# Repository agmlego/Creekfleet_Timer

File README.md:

Creekfleet Timer
================

Automated start sequencer for the [Creekfleet](https://creekfleet.org) sailing group.

By default, runs the following sequence for each of the number of requested starts:

| Horns             | Time to start |
| ----------------- | ------------- |
| 3 long            | 3:00          |
| 2 long            | 2:00          |
| 1 long, 3 short   | 1:30          |
| 1 long            | 1:00          |
| 3 short           | 0:30          |
| 2 short           | 0:20          |
| 1 short           | 0:10          |
| 1 short           | 0:05          |
| 1 short           | 0:04          |
| 1 short           | 0:03          |
| 1 short           | 0:02          |
| 1 short           | 0:01          |
| 1 long            | START         |

Also has a mode selectable during idle operation for the ISAF Rule 26 start:

| Horns             | Time to start |
| ----------------- | ------------- |
| 1 short           | 5:00          |
| 1 short           | 4:00          |
| 1 long            | 1:00          |
| 1 short           | START         |

## Pins

| Function      | Arduino Pin          |
| ------------- | -------------------- |
| Horn          | D12                  |
| Compressor    | D11                  |
| Pressure Gauge| D35 (A16)            |
| UP.LED        | D24                  |
| UP.Switch     | D25 (active low)     |
| DOWN.LED      | D26                  |
| DOWN.Switch   | D27 (active low)     |
| SELECT.LED    | D28                  |
| SELECT.Switch | D29 (active low)     |
| BACK.LED      | D30                  |
| BACK.Switch   | D31 (active low)     |
| LCD.VO        | A22 (DAC1)           |
| LCD.RS        | D13                  |
| LCD.RW        | D14                  |
| LCD.E         | D15                  |
| LCD.DB0       | D16                  |
| LCD.DB1       | D17                  |
| LCD.DB2       | D18                  |
| LCD.DB3       | D19                  |
| LCD.DB4       | D20                  |
| LCD.DB5       | D21                  |
| LCD.DB6       | D22                  |
| LCD.DB7       | D23                  |
| LCD.Red BL    | D36 (PWM)            |
| LCD.Green BL  | D38 (PWM)            |
| LCD.Blue BL   | D37 (PWM)            |

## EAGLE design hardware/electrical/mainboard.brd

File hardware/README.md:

Creekfleet Timer Hardware
=========================

EAGLE design files, case CAD files.

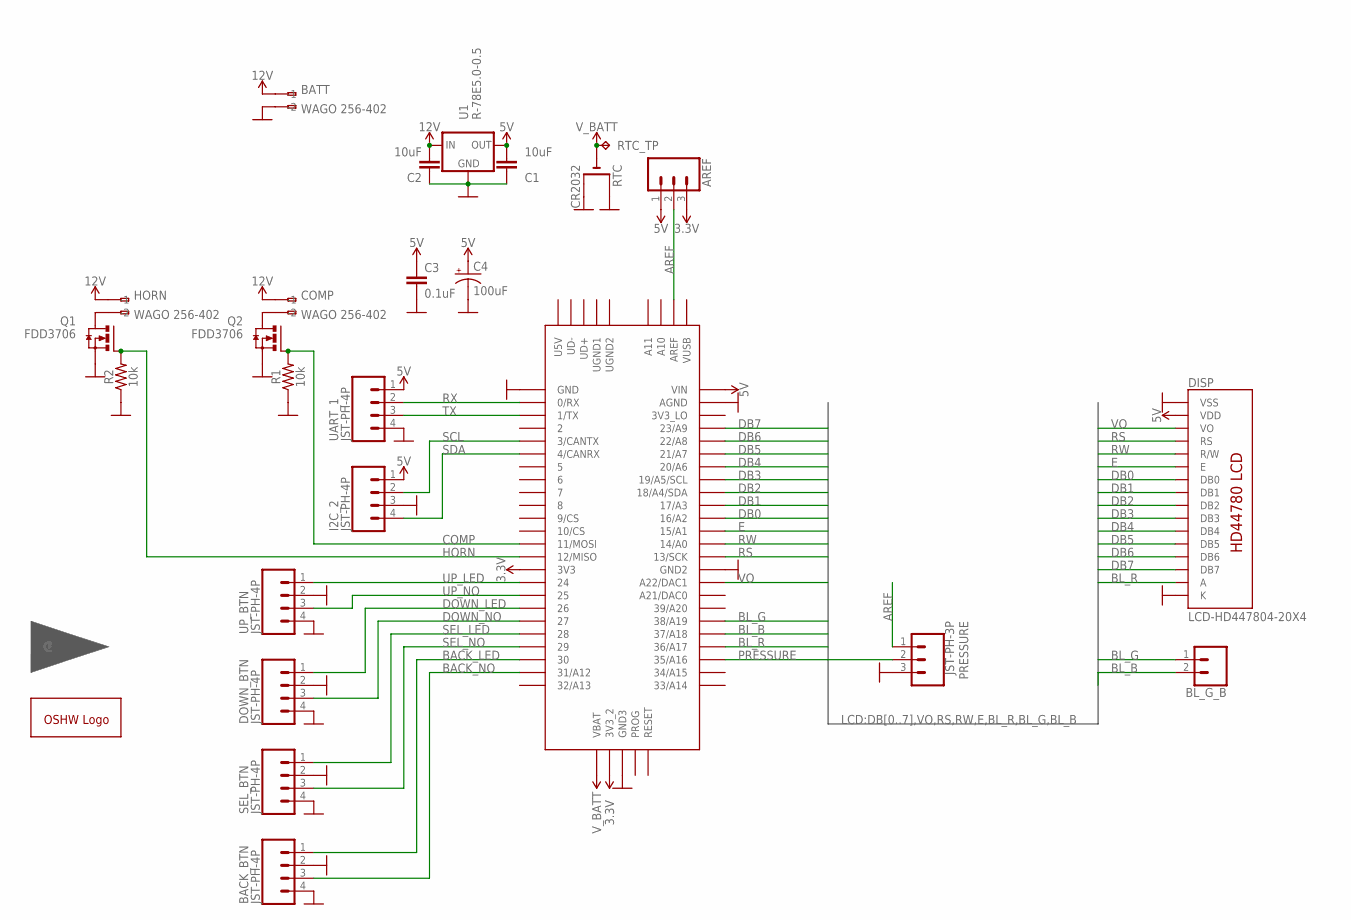
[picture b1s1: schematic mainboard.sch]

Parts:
AREF: CONN_03LOCK; 1X03_LOCK
BACK_BTN: JST-PH-4P; JST-4-PTH-VERT
BATT: WAGO 256-402; 255-402-5
BL_G_B: CONN_02; 1X02
C1, C2: 10uF; 0603
C3: 0.1uF; 0603
C4: 100uF; NIC_10X10.5_CAP
COMP: WAGO 256-402; 255-402-5
DISP: LCD-HD447804-20X4; LCD-20X4-4HOLES
DOWN_BTN: JST-PH-4P; JST-4-PTH-VERT
GOLD_ORB_SM1: OSHWLOGOLOGO8MM; OSHW_8MM
HORN: WAGO 256-402; 255-402-5
I2C_2: JST-PH-4P; JST-4-PTH-VERT
PRESSURE: JST-PH-3P; JST-3-PTH-VERT
Q1, Q2: FDD3706; D2PACK
R1, R2: 10k; 0603
RTC: CR2032; CR2032-SMD
RTC_TP: TPPAD1-17; P1-17
SEL_BTN: JST-PH-4P; JST-4-PTH-VERT
TEENSY: TEENSY_3.5/3.6
U1: R-78E5.0-0.5; DC-DC_CONVERTER_78XX
U$1: CFLOGO
UART_1: JST-PH-4P; JST-4-PTH-VERT
UP_BTN: JST-PH-4P; JST-4-PTH-VERT

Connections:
3.3V: AREF.3, TEENSY.3V3, TEENSY.3V3_2
5V: AREF.1, C1.2, C3.1, C4.+, DISP.P$2 (VDD), I2C_2.1, TEENSY.VIN, U1.VOUT (OUT), UART_1.1
12V: BATT.A1 (-1), C2.2, COMP.A1 (-1), HORN.A1 (-1), U1.VIN (IN)
AREF: AREF.2, PRESSURE.1, TEENSY.AREF
BACK_LED: BACK_BTN.1, TEENSY.30
BACK_NO: BACK_BTN.3, TEENSY.31/A12
BL_B: BL_G_B.2, TEENSY.37/A18
BL_G: BL_G_B.1, TEENSY.38/A19
BL_R: DISP.P$15 (A), TEENSY.36/A17
COMP: Q2.1 (G), R1.2, TEENSY.11/MOSI
DB0: DISP.P$7 (DB0), TEENSY.16/A2
DB1: DISP.P$8 (DB1), TEENSY.17/A3
DB2: DISP.P$9 (DB2), TEENSY.18/A4/SDA
DB3: DISP.P$10 (DB3), TEENSY.19/A5/SCL
DB4: DISP.P$11 (DB4), TEENSY.20/A6
DB5: DISP.P$12 (DB5), TEENSY.21/A7
DB6: DISP.P$13 (DB6), TEENSY.22/A8
DB7: DISP.P$14 (DB7), TEENSY.23/A9
DOWN_LED: DOWN_BTN.1, TEENSY.26
DOWN_NO: DOWN_BTN.3, TEENSY.27
E: DISP.P$6 (E), TEENSY.15/A1
GND: BACK_BTN.2, BACK_BTN.4, BATT.A2 (-2), C1.1, C2.1, C3.2, C4.-, DISP.P$1 (VSS), DISP.P$16 (K), DOWN_BTN.2, DOWN_BTN.4, I2C_2.3, PRESSURE.3, Q1.3 (S), Q2.3 (S), R1.1, R2.1, RTC.+$1 (+), RTC.+$2 (+1), SEL_BTN.2, SEL_BTN.4, TEENSY.AGND, TEENSY.GND, TEENSY.GND2, TEENSY.GND3, U1.GND, UART_1.4, UP_BTN.2, UP_BTN.4
HORN: Q1.1 (G), R2.2, TEENSY.12/MISO
unnamed: HORN.A2 (-2), Q1.2 (D)
unnamed: COMP.A2 (-2), Q2.2 (D)
PRESSURE: PRESSURE.2, TEENSY.35/A16
RS: DISP.P$4 (RS), TEENSY.13/SCK
RW: DISP.P$5 (R/W), TEENSY.14/A0
RX: TEENSY.0/RX, UART_1.2
SCL: I2C_2.2, TEENSY.3/CANTX
SDA: I2C_2.4, TEENSY.4/CANRX
SEL_LED: SEL_BTN.1, TEENSY.28
SEL_NO: SEL_BTN.3, TEENSY.29
TX: TEENSY.1/TX, UART_1.3
UP_LED: TEENSY.24, UP_BTN.1
UP_NO: TEENSY.25, UP_BTN.3
VO: DISP.P$3 (VO), TEENSY.A22/DAC1
V_BATT: RTC.-, RTC_TP.TP, TEENSY.VBAT

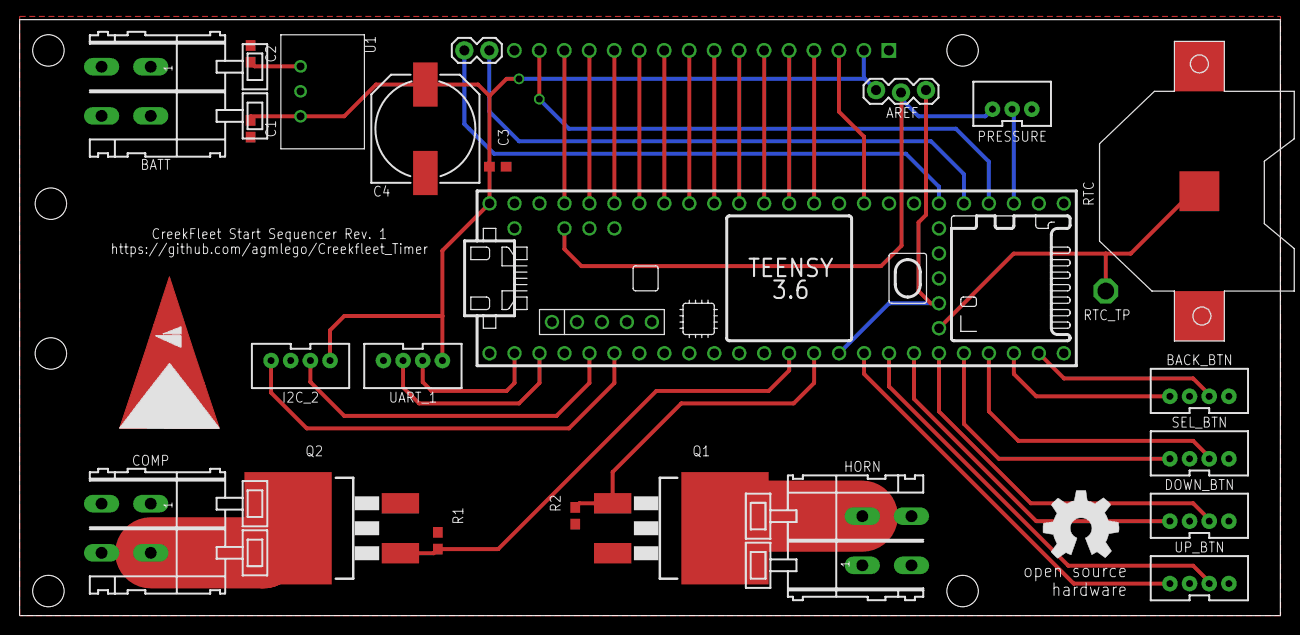
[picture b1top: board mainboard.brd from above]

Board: 2 copper layers, 128.2 x 60.6 mm, 27 parts (1 on the bottom side), 38 nets.

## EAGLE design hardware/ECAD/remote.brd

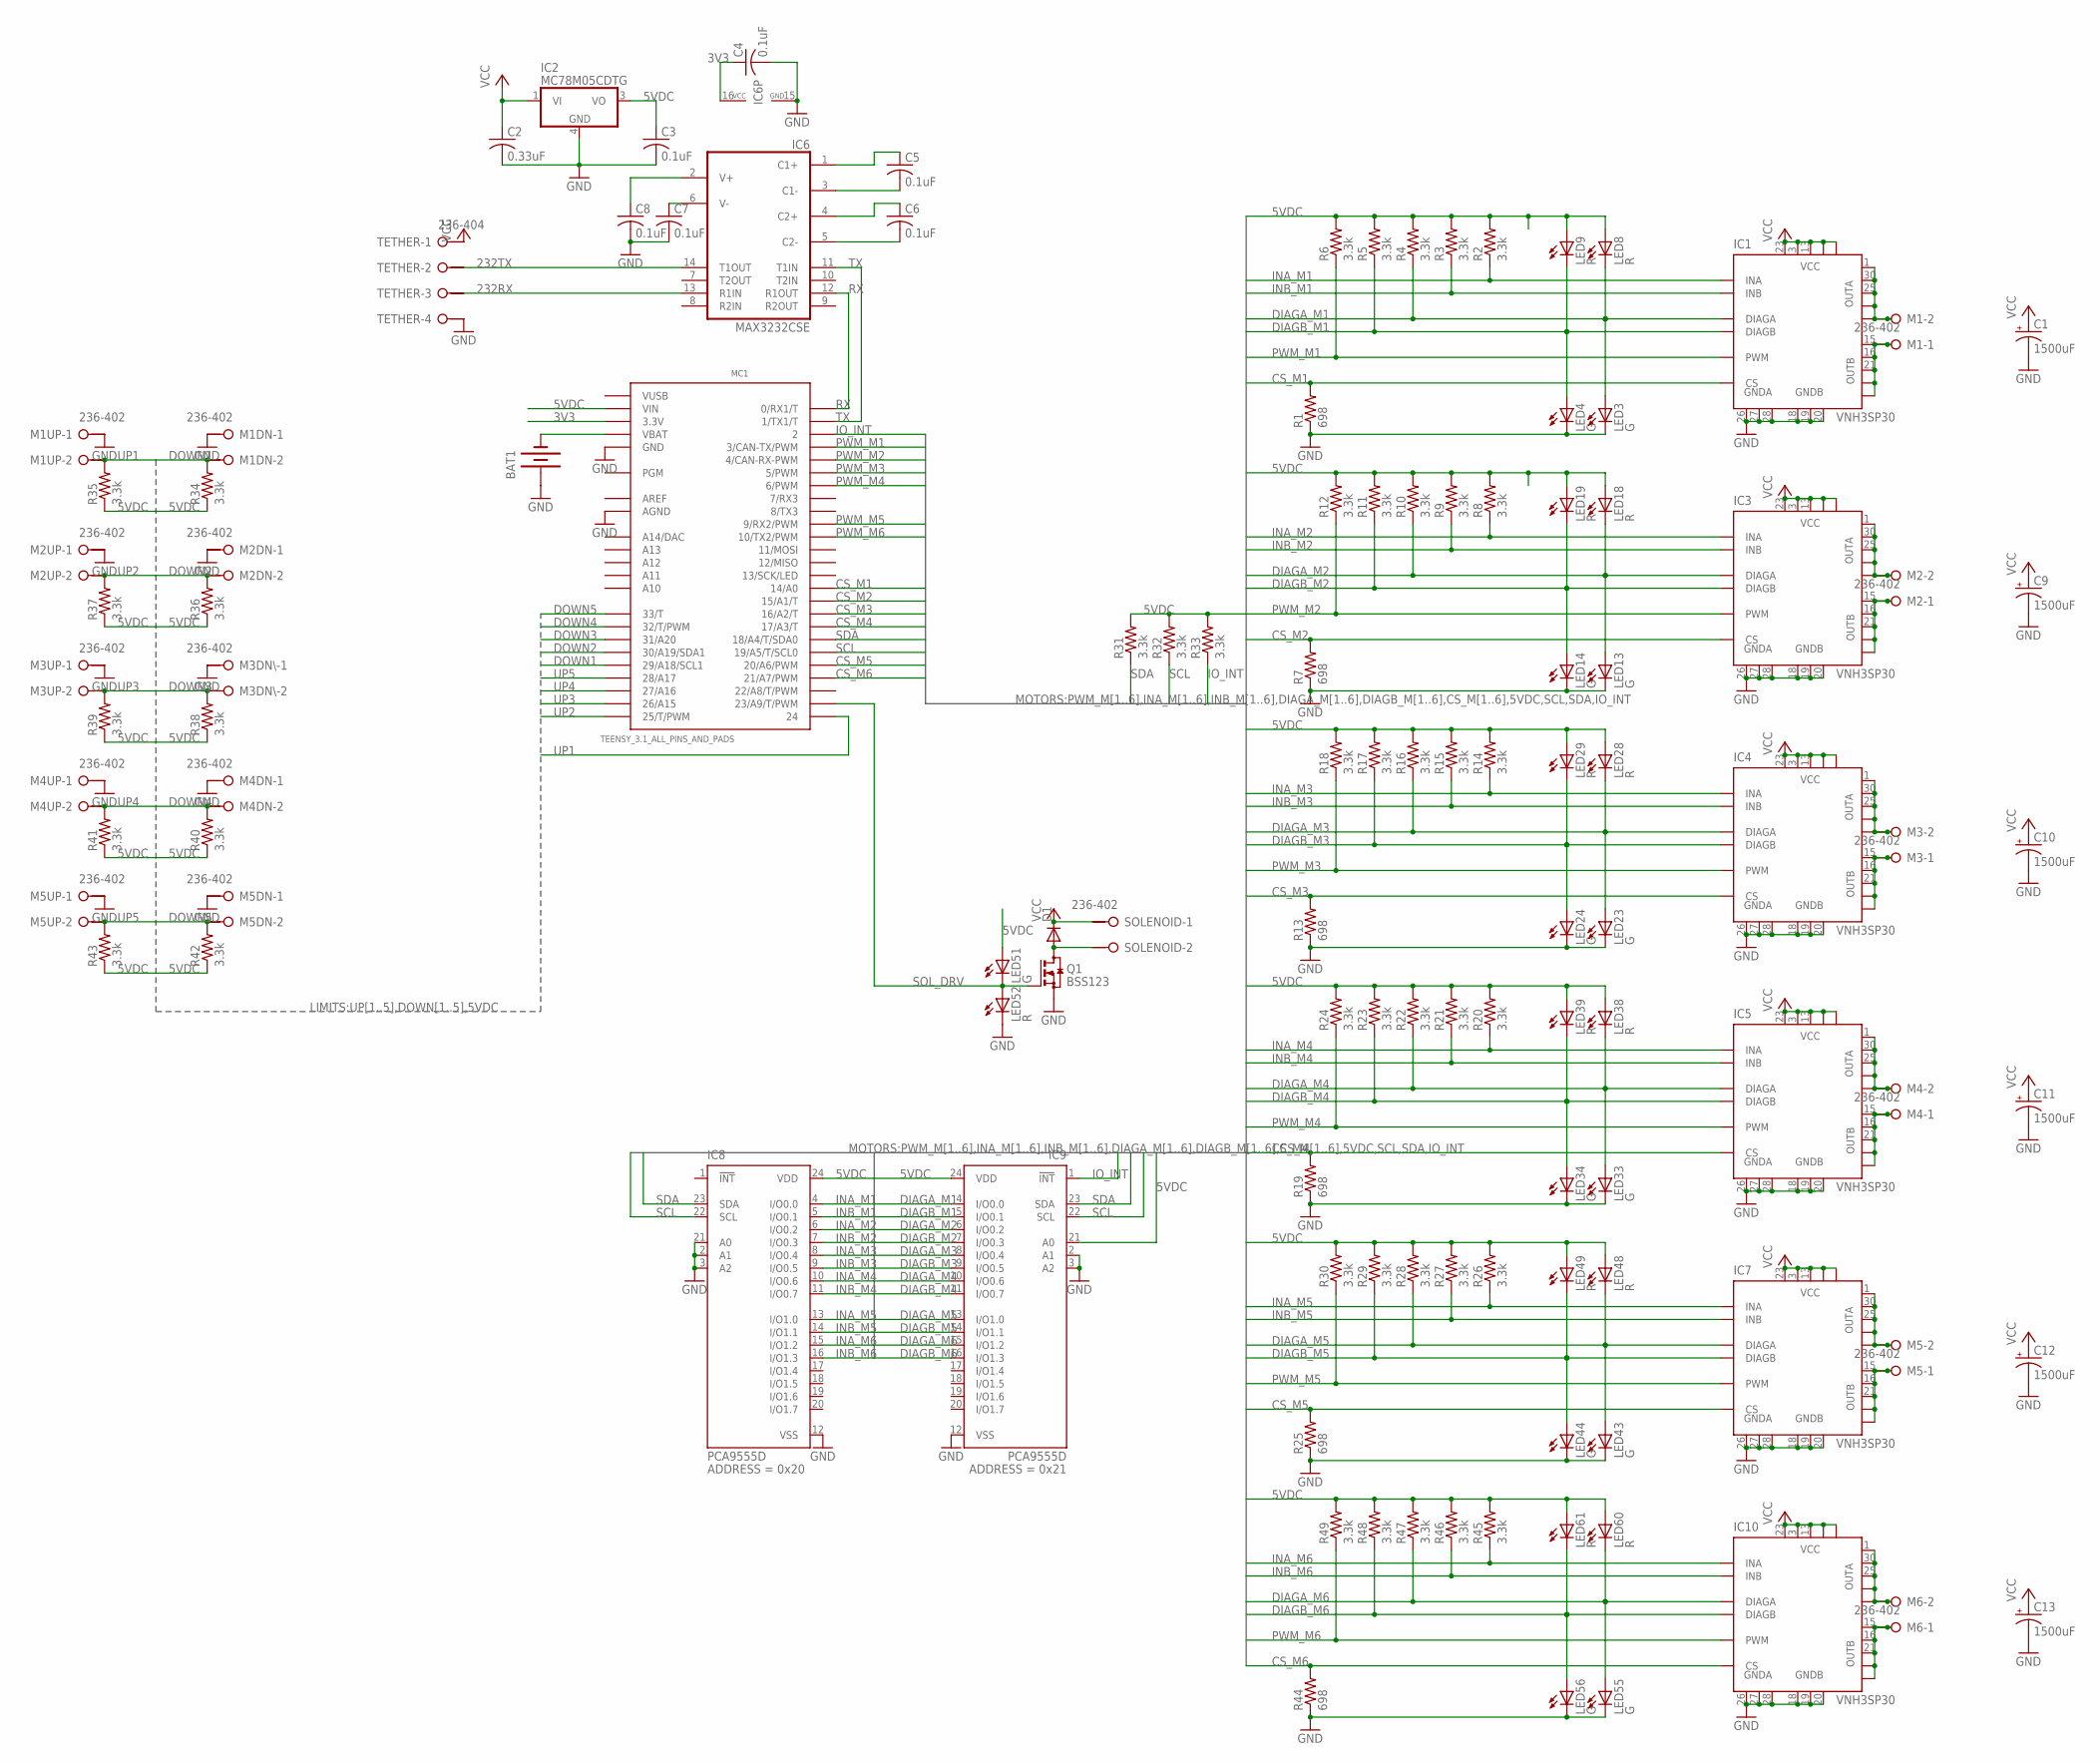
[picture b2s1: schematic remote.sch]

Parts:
BAT1: BATTERY20SMD; BATTCON_20MM
C1, C9, C10, C11, C12, C13: 1500uF; SANYO-OSCON_SMD_F12
C2: 0.33uF; C0805
C3, C4, C5, C6, C7, C8: 0.1uF; C0805
D1: DIODE-DO214AA; DO214AA
IC1, IC3, IC4, IC5, IC7, IC10: VNH3SP30; MULTIPOWERSO-30
IC2: MC78M05CDTG; DPACK_3
IC6: MAX3232CSE; SO16
IC8, IC9: PCA9555D; SO24
LED3, LED4, LED13, LED14, LED23, LED24, LED33, LED34, LED43, LED44, LED51, LED55, LED56: G; CHIP-LED0805
LED8, LED9, LED18, LED19, LED28, LED29, LED38, LED39, LED48, LED49, LED52, LED60, LED61: R; CHIP-LED0805
M1, M1DN, M1UP, M2, M2DN, M2UP, M3, M3DN\, M3UP, M4, M4DN, M4UP, M5, M5DN, M5UP, M6: 236-402
MC1: TEENSY_3.1_ALL_PINS_AND_PADS; TEENSY3_ALL_PINS_&_PADS
Q1: BSS123; SOT23
R1, R7, R13, R19, R25, R44: 698; R0805
R2, R3, R4, R5, R6, R8, R9, R10, R11, R12, R14, R15, R16, R17, R18, R20, R21, R22, R23, R24, R26, R27, R28, R29, R30, R31, R32, R33, R34, R35, R36, R37, R38, R39, R40, R41, R42, R43, R45, R46, R47, R48, R49: 3.3k; R0805
SOLENOID: 236-402
TETHER: 236-404

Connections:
3V3: C4.1, IC6.16 (VCC), MC1.3.3V, MC1.3.3V1 (3.3V), MC1.3.3V2 (3.3V)
5VDC: C3.1, IC2.3 (VO), IC8.24 (VDD), IC9.21 (A0), IC9.24 (VDD), LED8.A, LED9.A, LED18.A, LED19.A, LED28.A, LED29.A, LED38.A, LED39.A, LED48.A, LED49.A, LED51.A, LED60.A, LED61.A, MC1.VIN, R2.2, R3.2, R4.2, R5.2, R6.2, R8.2, R9.2, R10.2, R11.2, R12.2, R14.2, R15.2, R16.2, R17.2, R18.2, R20.2, R21.2, R22.2, R23.2, R24.2, R26.2, R27.2, R28.2, R29.2, R30.2, R31.2, R32.2, R33.2, R34.1, R35.1, R36.1, R37.1, R38.1, R39.1, R40.1, R41.1, R42.1, R43.1, R45.2, R46.2, R47.2, R48.2, R49.2
232RX: IC6.13 (R1IN), TETHER.3@1 (KL1)
232TX: IC6.14 (T1OUT), TETHER.2@1 (KL1)
AREF: MC1.AREF
CS_M1: IC1.9 (CS), MC1.14/A0, R1.2
CS_M2: IC3.9 (CS), MC1.15/A1 (15/A1/T), R7.2
CS_M3: IC4.9 (CS), MC1.16/A2 (16/A2/T), R13.2
CS_M4: IC5.9 (CS), MC1.17/A3 (17/A3/T), R19.2
CS_M5: IC7.9 (CS), MC1.20/A6 (20/A6/PWM), R25.2
CS_M6: IC10.9 (CS), MC1.21/A7 (21/A7/PWM), R44.2
DIAGA_M1: IC1.6 (DIAGA), IC9.4 (I/O0.0), LED3.A, LED8.C, R4.1
DIAGA_M2: IC3.6 (DIAGA), IC9.6 (I/O0.2), LED13.A, LED18.C, R10.1
DIAGA_M3: IC4.6 (DIAGA), IC9.8 (I/O0.4), LED23.A, LED28.C, R16.1
DIAGA_M4: IC5.6 (DIAGA), IC9.10 (I/O0.6), LED33.A, LED38.C, R22.1
DIAGA_M5: IC7.6 (DIAGA), IC9.13 (I/O1.0), LED43.A, LED48.C, R28.1
DIAGA_M6: IC9.15 (I/O1.2), IC10.6 (DIAGA), LED55.A, LED60.C, R47.1
DIAGB_M1: IC1.10 (DIAGB), IC9.5 (I/O0.1), LED4.A, LED9.C, R5.1
DIAGB_M2: IC3.10 (DIAGB), IC9.7 (I/O0.3), LED14.A, LED19.C, R11.1
DIAGB_M3: IC4.10 (DIAGB), IC9.9 (I/O0.5), LED24.A, LED29.C, R17.1
DIAGB_M4: IC5.10 (DIAGB), IC9.11 (I/O0.7), LED34.A, LED39.C, R23.1
DIAGB_M5: IC7.10 (DIAGB), IC9.14 (I/O1.1), LED44.A, LED49.C, R29.1
DIAGB_M6: IC9.16 (I/O1.3), IC10.10 (DIAGB), LED56.A, LED61.C, R48.1
DOWN1: M1DN.2@1 (KL1), MC1.29 (29/A18/SCL1), R34.2
DOWN2: M2DN.2@1 (KL1), MC1.30 (30/A19/SDA1), R36.2
DOWN3: M3DN\.2@1 (KL1), MC1.31 (31/A20), R38.2
DOWN4: M4DN.2@1 (KL1), MC1.32 (32/T/PWM), R40.2
DOWN5: M5DN.2@1 (KL1), MC1.33 (33/T), R42.2
GND: BAT1.1 (+), C1.-, C2.2, C3.2, C4.2, C7.2, C8.2, C9.-, C10.-, C11.-, C12.-, C13.-, IC1.18 (GNDB), IC1.19 (GNDB), IC1.20 (GNDB), IC1.26 (GNDA), IC1.27 (GNDA), IC1.28 (GNDA), IC2.4 (GND), IC3.18 (GNDB), IC3.19 (GNDB), IC3.20 (GNDB), IC3.26 (GNDA), IC3.27 (GNDA), IC3.28 (GNDA), IC4.18 (GNDB), IC4.19 (GNDB), IC4.20 (GNDB), IC4.26 (GNDA), IC4.27 (GNDA), IC4.28 (GNDA), IC5.18 (GNDB), IC5.19 (GNDB), IC5.20 (GNDB), IC5.26 (GNDA), IC5.27 (GNDA), IC5.28 (GNDA), IC6.15 (GND), IC7.18 (GNDB), IC7.19 (GNDB), IC7.20 (GNDB), IC7.26 (GNDA), IC7.27 (GNDA), IC7.28 (GNDA), IC8.2 (A1), IC8.3 (A2), IC8.12 (VSS), IC8.21 (A0), IC9.2 (A1), IC9.3 (A2), IC9.12 (VSS), IC10.18 (GNDB), IC10.19 (GNDB), IC10.20 (GNDB), IC10.26 (GNDA), IC10.27 (GNDA), IC10.28 (GNDA), LED3.C, LED4.C, LED13.C, LED14.C, LED23.C, LED24.C, LED33.C, LED34.C, LED43.C, LED44.C, LED52.C, LED55.C, LED56.C, M1DN.1@1 (KL1), M1UP.1@1 (KL1), M2DN.1@1 (KL1), M2UP.1@1 (KL1), M3DN\.1@1 (KL1), M3UP.1@1 (KL1), M4DN.1@1 (KL1), M4UP.1@1 (KL1), M5DN.1@1 (KL1), M5UP.1@1 (KL1), MC1.AGND, MC1.GND, MC1.GND1 (GND), MC1.GND2 (GND), Q1.2 (S), R1.1, R7.1, R13.1, R19.1, R25.1, R44.1, TETHER.4@1 (KL1)
INA_M1: IC1.5 (INA), IC8.4 (I/O0.0), R2.1
INA_M2: IC3.5 (INA), IC8.6 (I/O0.2), R8.1
INA_M3: IC4.5 (INA), IC8.8 (I/O0.4), R14.1
INA_M4: IC5.5 (INA), IC8.10 (I/O0.6), R20.1
INA_M5: IC7.5 (INA), IC8.13 (I/O1.0), R26.1
INA_M6: IC8.15 (I/O1.2), IC10.5 (INA), R45.1
INB_M1: IC1.11 (INB), IC8.5 (I/O0.1), R3.1
INB_M2: IC3.11 (INB), IC8.7 (I/O0.3), R9.1
INB_M3: IC4.11 (INB), IC8.9 (I/O0.5), R15.1
INB_M4: IC5.11 (INB), IC8.11 (I/O0.7), R21.1
INB_M5: IC7.11 (INB), IC8.14 (I/O1.1), R27.1
INB_M6: IC8.16 (I/O1.3), IC10.11 (INB), R46.1
IO_INT: IC9.1 (!INT), MC1.2, R33.1
M1A: IC1.1 (OUTA), IC1.25 (OUTA), IC1.30 (OUTA), IC1.OUTA, IC1.OUTA@1 (OUTA), M1.2@1 (KL1), M1.2@2 (KL2)
M1B: IC1.15 (OUTB), IC1.16 (OUTB), IC1.21 (OUTB), IC1.OUTB, IC1.OUTB@1 (OUTB), M1.1@1 (KL1), M1.1@2 (KL2)
M2A: IC3.1 (OUTA), IC3.25 (OUTA), IC3.30 (OUTA), IC3.OUTA, IC3.OUTA@1 (OUTA), M2.2@1 (KL1), M2.2@2 (KL2)
M2B: IC3.15 (OUTB), IC3.16 (OUTB), IC3.21 (OUTB), IC3.OUTB, IC3.OUTB@1 (OUTB), M2.1@1 (KL1), M2.1@2 (KL2)
M3A: IC4.1 (OUTA), IC4.25 (OUTA), IC4.30 (OUTA), IC4.OUTA, IC4.OUTA@1 (OUTA), M3.2@1 (KL1), M3.2@2 (KL2)
M3B: IC4.15 (OUTB), IC4.16 (OUTB), IC4.21 (OUTB), IC4.OUTB, IC4.OUTB@1 (OUTB), M3.1@1 (KL1), M3.1@2 (KL2)
M4A: IC5.1 (OUTA), IC5.25 (OUTA), IC5.30 (OUTA), IC5.OUTA, IC5.OUTA@1 (OUTA), M4.2@1 (KL1), M4.2@2 (KL2)
M4B: IC5.15 (OUTB), IC5.16 (OUTB), IC5.21 (OUTB), IC5.OUTB, IC5.OUTB@1 (OUTB), M4.1@1 (KL1), M4.1@2 (KL2)
M5A: IC7.1 (OUTA), IC7.25 (OUTA), IC7.30 (OUTA), IC7.OUTA, IC7.OUTA@1 (OUTA), M5.2@1 (KL1), M5.2@2 (KL2)
M5B: IC7.15 (OUTB), IC7.16 (OUTB), IC7.21 (OUTB), IC7.OUTB, IC7.OUTB@1 (OUTB), M5.1@1 (KL1), M5.1@2 (KL2)
M6A: IC10.1 (OUTA), IC10.25 (OUTA), IC10.30 (OUTA), IC10.OUTA, IC10.OUTA@1 (OUTA), M6.2@1 (KL1), M6.2@2 (KL2)
M6B: IC10.15 (OUTB), IC10.16 (OUTB), IC10.21 (OUTB), IC10.OUTB, IC10.OUTB@1 (OUTB), M6.1@1 (KL1), M6.1@2 (KL2)
unnamed: C5.1, IC6.1 (C1+)
unnamed: C5.2, IC6.3 (C1-)
unnamed: C6.1, IC6.4 (C2+)
unnamed: C6.2, IC6.5 (C2-)
unnamed: C8.1, IC6.2 (V+)
unnamed: C7.1, IC6.6 (V-)
unnamed: BAT1.2 (-), MC1.VBAT
unnamed: D1.A, Q1.3 (D), SOLENOID.2@1 (KL1)
PWM_M1: IC1.8 (PWM), MC1.3 (3/CAN-TX/PWM), R6.1
PWM_M2: IC3.8 (PWM), MC1.4 (4/CAN-RX-PWM), R12.1
PWM_M3: IC4.8 (PWM), MC1.5 (5/PWM), R18.1
PWM_M4: IC5.8 (PWM), MC1.6 (6/PWM), R24.1
PWM_M5: IC7.8 (PWM), MC1.9 (9/RX2/PWM), R30.1
PWM_M6: IC10.8 (PWM), MC1.10 (10/TX2/PWM), R49.1
RX: IC6.12 (R1OUT), MC1.0 (0/RX1/T)
SCL: IC8.22 (SCL), IC9.22 (SCL), MC1.19/A5 (19/A5/T/SCL0), R32.1
SDA: IC8.23 (SDA), IC9.23 (SDA), MC1.18/A4 (18/A4/T/SDA0), R31.1
SOL_DRV: LED51.C, LED52.A, MC1.23/A9 (23/A9/T/PWM), Q1.1 (G)
TX: IC6.11 (T1IN), MC1.1 (1/TX1/T)
UP1: M1UP.2@1 (KL1), MC1.24, R35.2
UP2: M2UP.2@1 (KL1), MC1.25 (25/T/PWM), R37.2
UP3: M3UP.2@1 (KL1), MC1.26 (26/A15), R39.2
UP4: M4UP.2@1 (KL1), MC1.27 (27/A16), R41.2
UP5: M5UP.2@1 (KL1), MC1.28 (28/A17), R43.2
VCC: C1.+, C2.1, C9.+, C10.+, C11.+, C12.+, C13.+, D1.C, IC1.3 (VCC), IC1.13 (VCC), IC1.23 (VCC), IC1.VCC, IC1.VCC@1 (VCC), IC2.1 (VI), IC3.3 (VCC), IC3.13 (VCC), IC3.23 (VCC), IC3.VCC, IC3.VCC@1 (VCC), IC4.3 (VCC), IC4.13 (VCC), IC4.23 (VCC), IC4.VCC, IC4.VCC@1 (VCC), IC5.3 (VCC), IC5.13 (VCC), IC5.23 (VCC), IC5.VCC, IC5.VCC@1 (VCC), IC7.3 (VCC), IC7.13 (VCC), IC7.23 (VCC), IC7.VCC, IC7.VCC@1 (VCC), IC10.3 (VCC), IC10.13 (VCC), IC10.23 (VCC), IC10.VCC, IC10.VCC@1 (VCC), SOLENOID.1@1 (KL1), TETHER.1@1 (KL1)
VUSB: MC1.VUSB

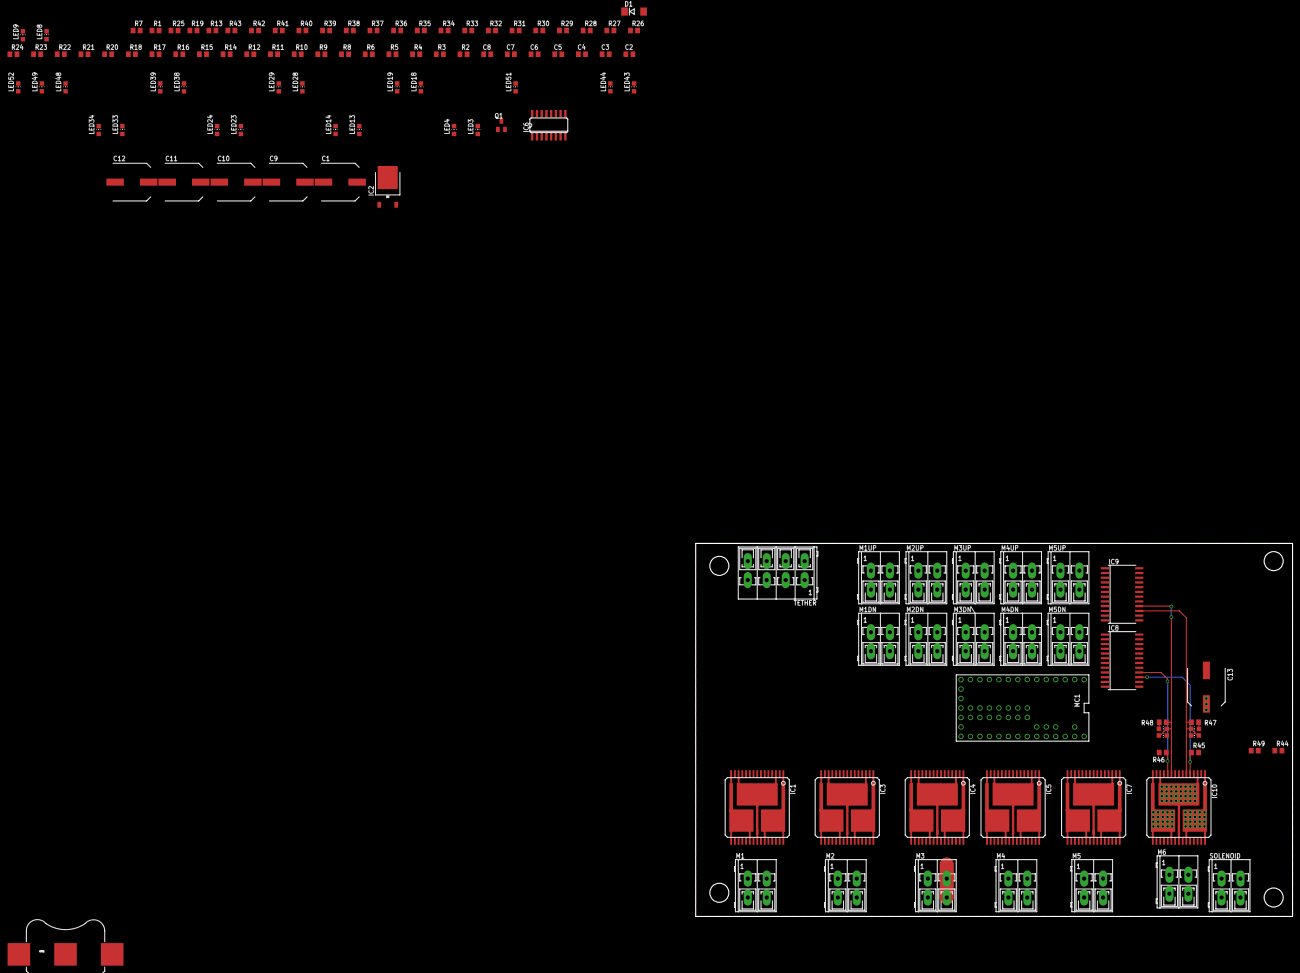
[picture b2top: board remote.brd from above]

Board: 2 copper layers, 160.0 x 100.0 mm, 120 parts (0 on the bottom side), 78 nets.

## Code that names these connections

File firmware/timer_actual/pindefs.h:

#define HORN            12
#define COMPRESSOR      11
#define PRESSURE        A16
#define UP_LED          24
#define UP_SWITCH       25
#define DOWN_LED        26
#define DOWN_SWITCH     27
#define SELECT_LED      28
#define SELECT_SWITCH   29
#define BACK_LED        30
#define BACK_SWITCH     31
#define LCD_VO          A22
#define LCD_RS          13
#define LCD_RW          14
#define LCD_E           15
#define LCD_DB0         16
#define LCD_DB1         17
#define LCD_DB2         18
#define LCD_DB3         19
#define LCD_DB4         20
#define LCD_DB5         21
#define LCD_DB6         22
#define LCD_DB7         23
#define LCD_BL_RED      36
#define LCD_BL_BLUE     37
#define LCD_BL_GREEN    38

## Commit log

2014-04-05 Initial commit, with READMEs for the directory structure, and a starting example for LCD display.
2014-04-05 Pin setup complete, header file populated.
2014-04-06 Added some time values and sketched out ISRs.
2014-06-05 Test code to get sequence correct.
2015-06-09 Added looped sequence to accomodate multiple starts.
2015-06-17 Reduced starts to 1 (not as many boats of a class showing up as we expected...maybe later). Changed inter-start delay to 60s.
2016-06-01 Update with CAD, board files, and new firmware.
2016-06-08 Laid out compressor driver.
2016-07-09 Cleaned up code for data types, assigned flag pins for remote, modified README.md with pin assignments.
2016-07-09 Drawings created for prints (machining) and printing (drill hole spotting). STL created for 3D printing.
2016-08-13 Added connector details for remote
2016-08-13 Corrected image links
    Using rawgit to serve connector images, per isaacs/github#316
2017-09-04 Leftover changes from decommissioned machine
2021-02-28 Preparation for new design, horns-only
2021-02-28 New board design for horn-only operation
2021-02-28 added testpoint for RTC battery
2021-02-28 Fixed copper under CR2032 holder
2021-03-04 Added CAD for case panel
2021-03-07 "Pin definitions and some setup."
2021-03-07 "All pins configured, compressor periodic task configured, beginning of RTC setup"
2021-03-07 "Time print from RTC"
2021-05-18 Conversion to PlatformIO project
2021-05-18 Added PDF board art
2021-05-19 Power-on LED test
2021-05-19 Got RTC set and displaying on screen
2021-05-19 Working MVP; added Python script to generate horn sequence in horns.h
2021-05-19 Removed original Arduino firmware
2021-10-21 Added harness drawing.
2021-10-21 Added ISAF 5-minute Rule 26 start
2021-10-21 Selectable sequence
2021-10-21 Minimize flicker in idle
2022-10-04 Fixes issue #6

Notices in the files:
parts and their libraries:
SparkFun-Electromechanical: Licensing: Creative Commons ShareAlike 4.0 International - https://creativecommons.org/licenses/by-sa/4.0
